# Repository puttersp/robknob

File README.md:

# robknob
## Robknob is a smartknob for robotics.
### FEATURES
- Smartknob with Haptic feedback
    - 3 Hapfic feedback modes
        - Fine steps with low detents
        - Rough steps with medium detents
        - Fine steps with medium detents and Bounded with high detents
    - Press for mode change
        - 3 steps press with strain gauges
            - Different colors displayed by LED Strips for different steps
        - LiDAR Mode for Robot Navigation
        - PID Tuning Mode
        - IMU Display
    - 240x240 Round LCD Display
- LiDAR with 4000Hz Sampling Rate 5M Range
- 6-DOF IMU for Robot Navigation
- ROS2 Compatible

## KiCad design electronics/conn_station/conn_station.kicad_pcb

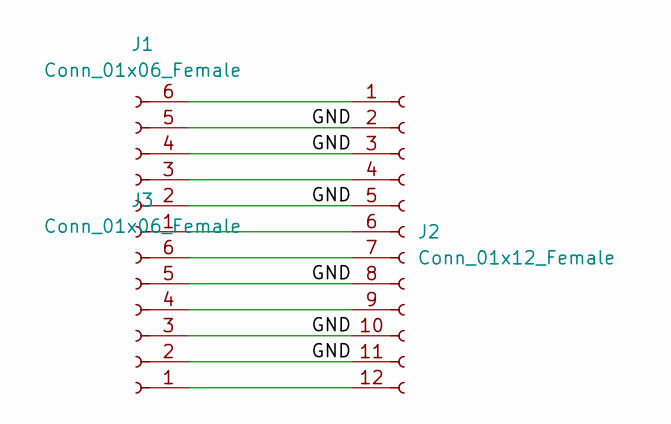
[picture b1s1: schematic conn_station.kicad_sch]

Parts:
J1, J3: Conn_01x06_Female; PinSocket_1x06_P2.54mm_Horizontal
J2: Conn_01x12_Female; Molex_200528-0120_1x12-1MP_P1.00mm_Horizontal

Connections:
/GND: J1.2, J1.4, J1.5, J2.2, J2.3, J2.5, J2.8, J2.10, J2.11, J2.MP, J3.2, J3.3, J3.5
unnamed: J1.1, J2.6
unnamed: J1.3, J2.4
unnamed: J1.6, J2.1
unnamed: J2.7, J3.6
unnamed: J2.9, J3.4
unnamed: J2.12, J3.1

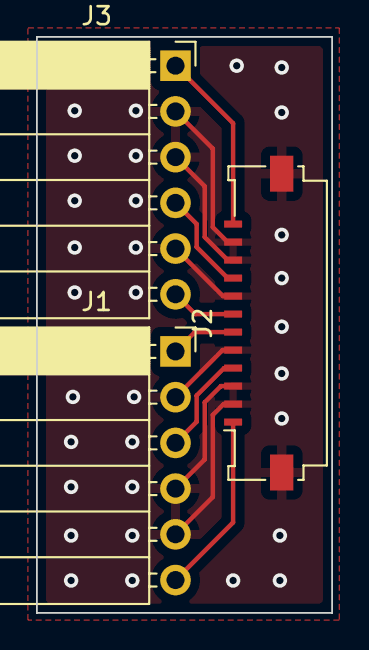
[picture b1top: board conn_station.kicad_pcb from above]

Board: 2 copper layers, 16.4 x 32.0 mm, 3 parts (0 on the bottom side), 7 nets.

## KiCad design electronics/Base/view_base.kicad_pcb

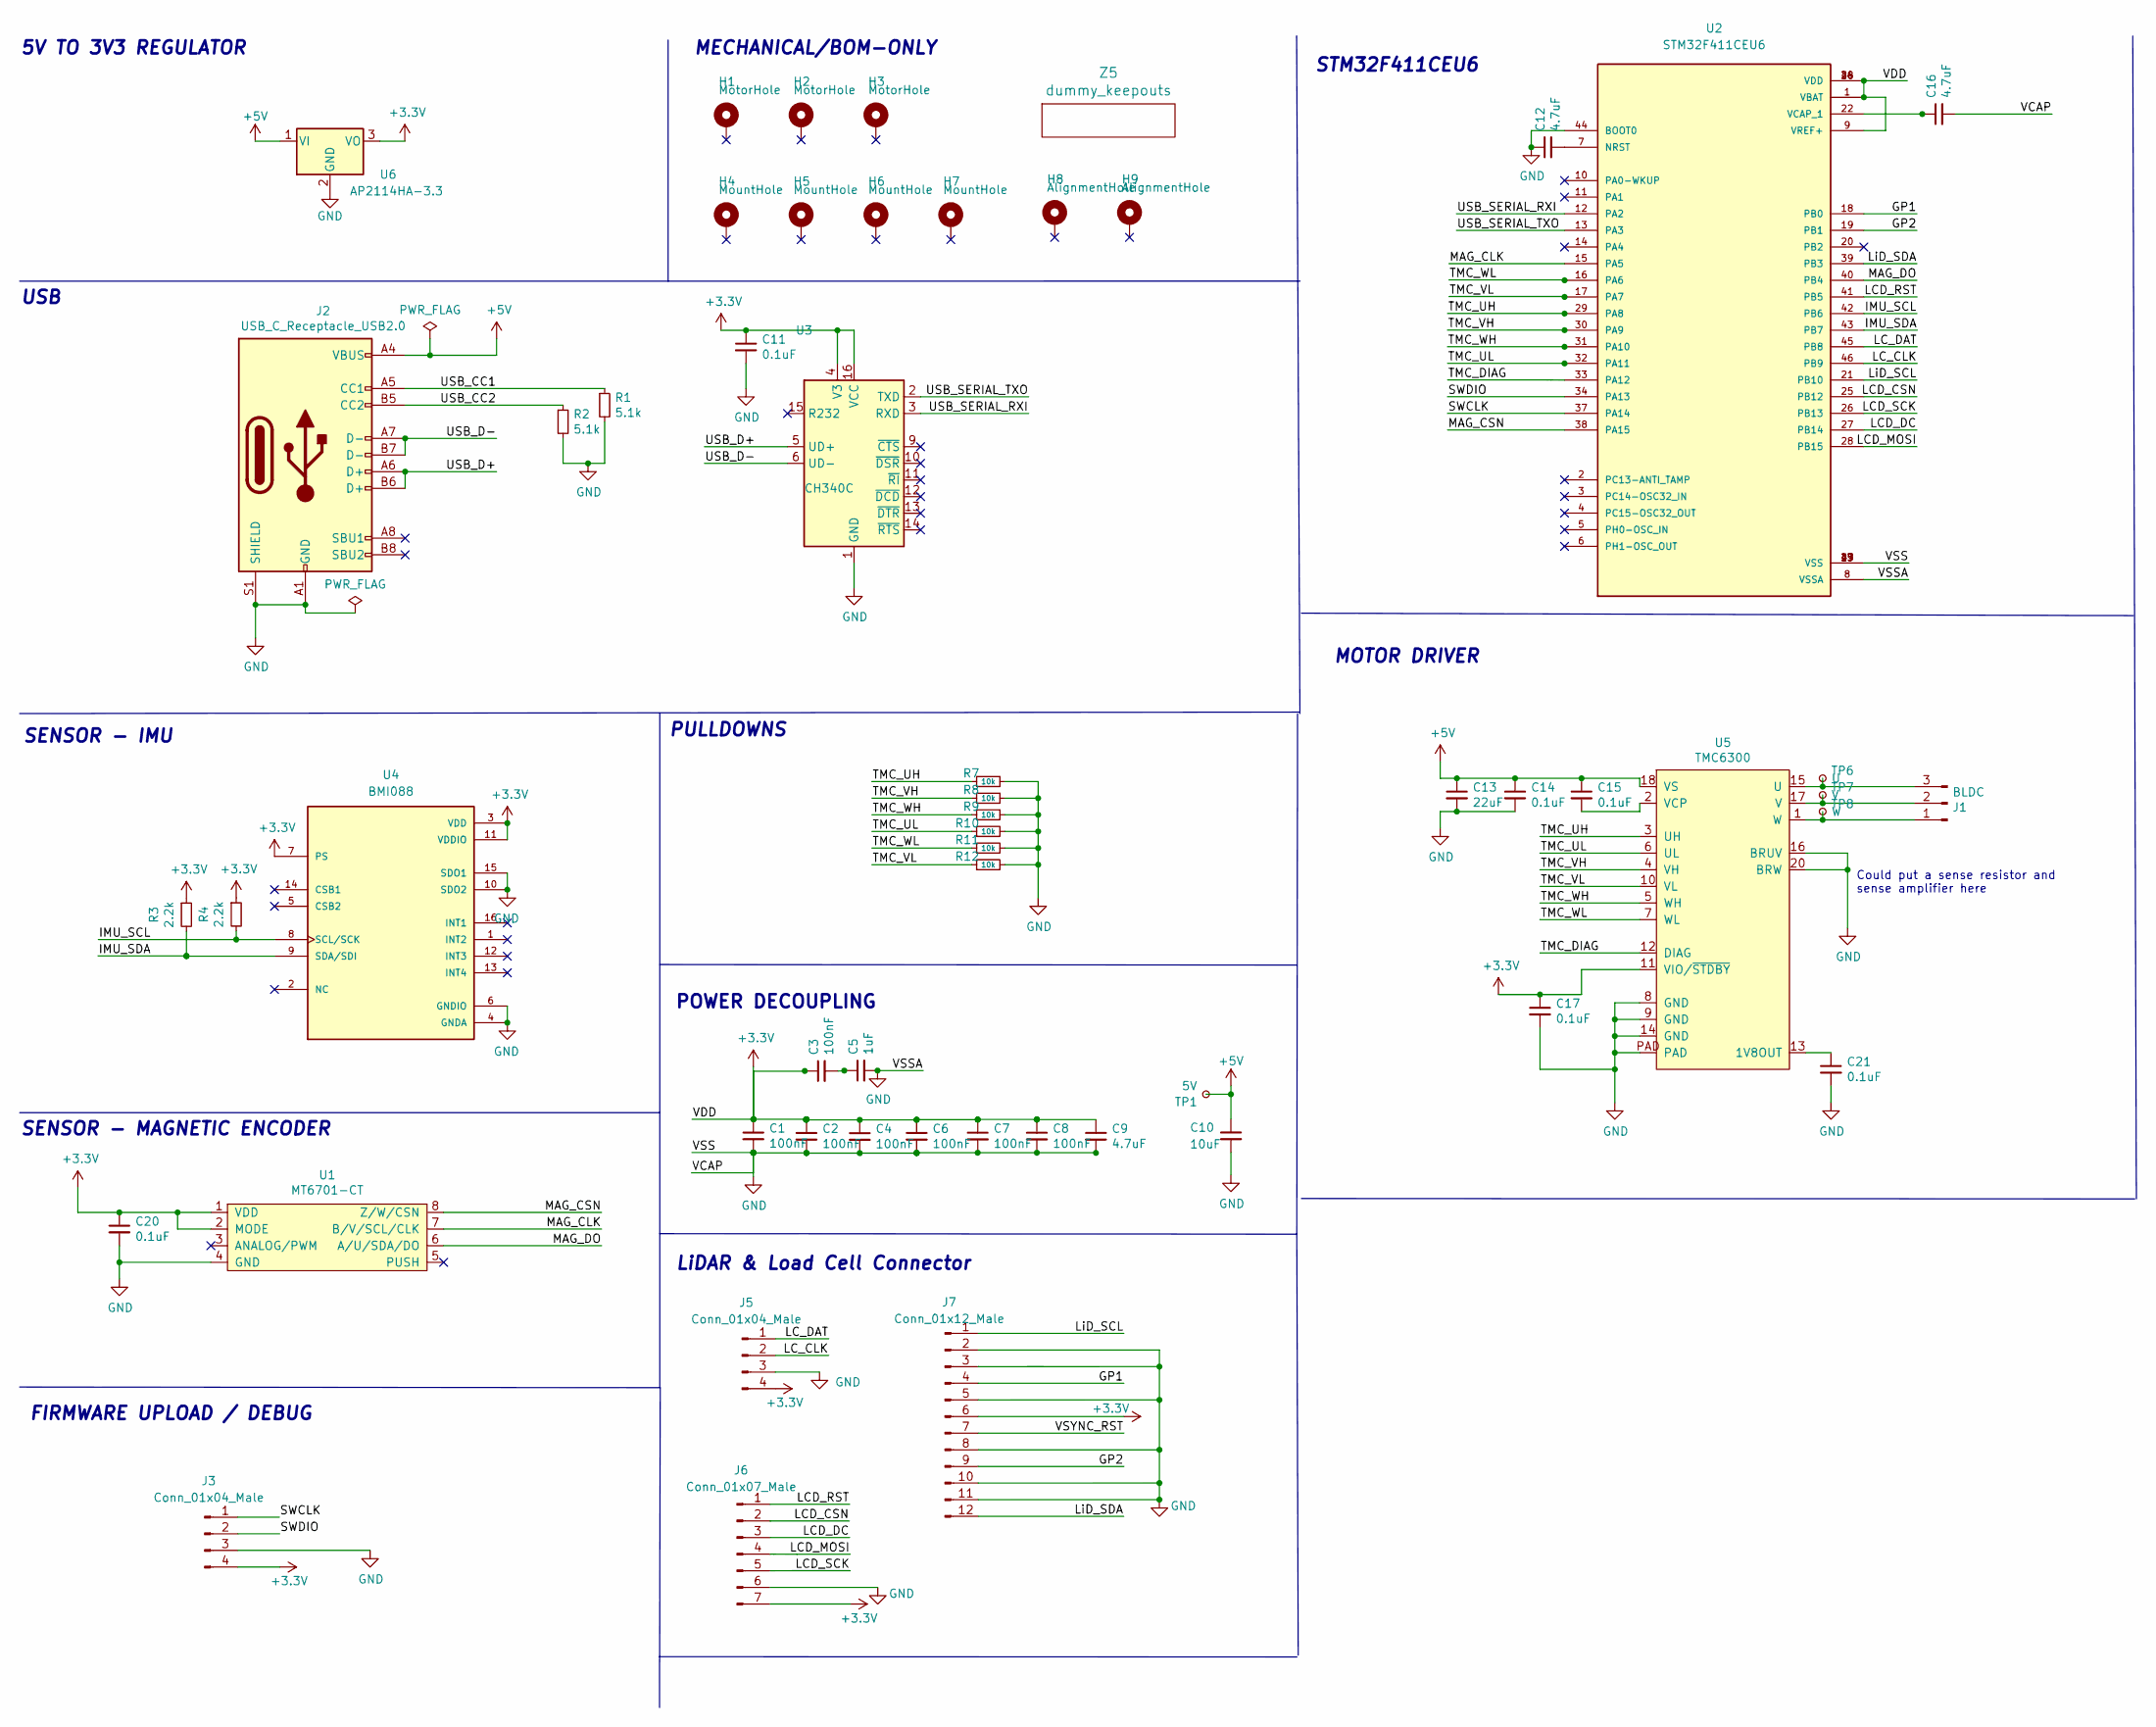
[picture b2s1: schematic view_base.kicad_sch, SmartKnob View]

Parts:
C1, C2, C3, C4, C6, C7, C8: 100nF; C_0603_1608Metric; LCSC C1591
C5: 1uF; C_0603_1608Metric; LCSC C1591
C9, C12, C16: 4.7uF; C_0603_1608Metric; LCSC C1591
C10: 10uF; C_0805_2012Metric; LCSC C2922480
C11, C14, C15, C17, C20, C21: 0.1uF; C_0603_1608Metric; LCSC C1591
C13: 22uF; C_0805_2012Metric; LCSC C98190
H1, H2, H3: MotorHole; MountingHole_M1.6; LCSC C2931389
H4, H5, H6, H7: MountHole; MountingHole_2.2mm_M2_ISO7380_Pad_NonVirtual; LCSC C2911210 or C2911532 (screw), C2961595 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
H8, H9: AlignmentHole; MountingHole_2.2mm_M2_ISO7380_Pad_NonVirtual
J1: BLDC; 532610371; LCSC C293630
J2: USB_C_Receptacle_USB2.0; USB4510_NoPaste; LCSC C428463
J3, J5: Conn_01x04_Male; PinHeader_1x04_P2.54mm_Vertical
J6: Conn_01x07_Male; PinHeader_1x07_P2.54mm_Vertical
J7: Conn_01x12_Male; Molex_200528-0120_1x12-1MP_P1.00mm_Horizontal
R1, R2: 5.1k; R_0603_1608Metric; LCSC C105580
R3, R4: 2.2k; R_0603_1608Metric; LCSC C4190
R7, R8, R9, R10, R11, R12: 10k; R_0603_1608Metric; LCSC C98220
TP1: 5V; TestPoint_Pad_D2.0mm_ValueSilk
TP6: U; TestPoint_Pad_D2.0mm_ValueSilk
TP7: V; TestPoint_Pad_D2.0mm_ValueSilk
TP8: W; TestPoint_Pad_D2.0mm_ValueSilk
U1: MT6701-CT; SOIC-8_3.9x4.9mm_P1.27mm; LCSC C2856764, or C3003196
U2: STM32F411CEU6; QFN50P700X700X60-49N; PARTREV 7
U3: CH340C; SOIC-16_3.9x9.9mm_P1.27mm; LCSC C84681
U4: BMI088; PQFN50P450X300X100-16N
U5: TMC6300; QFN-20-1EP_3x3mm_P0.4mm_EP1.65x1.65mm_ThermalVias_LargerVia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; Digikey TMC6300-LA-T
U6: AP2114HA-3.3; SOT-223-3_TabPin2_InGndOut; LCSC C460314
Z5: dummy_keepouts; ViewKeepouts3d

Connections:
+3V3: C1.1, C2.1, C3.1, C4.1, C6.1, C7.1, C8.1, C9.1, C11.1, C17.1, C20.1, J3.4, J5.4, J6.7, J7.6, R3.1, R4.1, U1.1 (VDD), U1.2 (MODE), U2.1 (VBAT), U2.9 (VREF+), U2.24 (VDD), U2.36 (VDD), U2.48 (VDD), U3.4 (V3), U3.16 (VCC), U4.3 (VDD), U4.7 (PS), U4.11 (VDDIO), U5.11 (VIO/~STDBY), U6.3 (VO)
+5V: C10.1, C13.1, C14.1, C15.1, J2.A4 (VBUS), J2.A9 (VBUS), J2.B4 (VBUS), J2.B9 (VBUS), TP1.1, U5.18 (VS), U6.1 (VI)
/GP1: J7.4, U2.18 (PB0)
/GP2: J7.9, U2.19 (PB1)
/IMU_SCL: R4.2, U2.42 (PB6), U4.8 (SCL/SCK)
/IMU_SDA: R3.2, U2.43 (PB7), U4.9 (SDA/SDI)
/LCD_CSN: J6.2, U2.25 (PB12)
/LCD_DC: J6.3, U2.27 (PB14)
/LCD_MOSI: J6.4, U2.28 (PB15)
/LCD_RST: J6.1, U2.41 (PB5)
/LCD_SCK: J6.5, U2.26 (PB13)
/LC_CLK: J5.2, U2.46 (PB9)
/LC_DAT: J5.1, U2.45 (PB8)
/LiD_SCL: J7.1, U2.21 (PB10)
/LiD_SDA: J7.12, U2.39 (PB3)
/MAG_CLK: U1.7 (B/V/SCL/CLK), U2.15 (PA5)
/MAG_CSN: U1.8 (Z/W/CSN), U2.38 (PA15)
/MAG_DO: U1.6 (A/U/SDA/DO), U2.40 (PB4)
/SWCLK: J3.1, U2.37 (PA14)
/SWDIO: J3.2, U2.34 (PA13)
/TMC_DIAG: U2.33 (PA12), U5.12 (DIAG)
/TMC_UH: R7.1, U2.29 (PA8), U5.3 (UH)
/TMC_UL: R10.1, U2.32 (PA11), U5.6 (UL)
/TMC_VH: R8.1, U2.30 (PA9), U5.4 (VH)
/TMC_VL: R12.1, U2.17 (PA7), U5.10 (VL)
/TMC_WH: R9.1, U2.31 (PA10), U5.5 (WH)
/TMC_WL: R11.1, U2.16 (PA6), U5.7 (WL)
/USB_CC1: J2.A5 (CC1), R1.1
/USB_CC2: J2.B5 (CC2), R2.1
/USB_D+: J2.A6 (D+), J2.B6 (D+), U3.5 (UD+)
/USB_D-: J2.A7 (D-), J2.B7 (D-), U3.6 (UD-)
/USB_SERIAL_RXI: U2.12 (PA2), U3.3 (RXD)
/USB_SERIAL_TXO: U2.13 (PA3), U3.2 (TXD)
/VSYNC_RST: J7.7
GND: C1.2, C2.2, C4.2, C5.2, C6.2, C7.2, C8.2, C9.2, C10.2, C11.2, C12.1, C13.2, C14.2, C16.2, C17.2, C20.2, C21.2, J2.A1 (GND), J2.A12 (GND), J2.B1 (GND), J2.B12 (GND), J2.S1 (SHIELD), J3.3, J5.3, J6.6, J7.2, J7.3, J7.5, J7.8, J7.10, J7.11, J7.MP, R1.2, R2.2, R7.2, R8.2, R9.2, R10.2, R11.2, R12.2, U1.4 (GND), U2.8 (VSSA), U2.23 (VSS), U2.35 (VSS), U2.44 (BOOT0), U2.47 (VSS), U2.49 (VSS), U3.1 (GND), U4.4 (GNDA), U4.6 (GNDIO), U4.10 (SDO2), U4.15 (SDO1), U5.8 (GND), U5.9 (GND), U5.14 (GND), U5.16 (BRUV), U5.20 (BRW), U5.PAD, U6.2 (GND)
unnamed: C3.2, C5.1
unnamed: C12.2, U2.7 (NRST)
unnamed: C15.2, U5.2 (VCP)
unnamed: C16.1, U2.22 (VCAP_1)
unnamed: C21.1, U5.13 (1V8OUT)
unnamed: J1.1, TP8.1, U5.1 (W)
unnamed: J1.2, TP7.1, U5.17 (V)
unnamed: J1.3, TP6.1, U5.15 (U)

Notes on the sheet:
5V TO 3V3 REGULATOR
Could put a sense resistor and sense amplifier here
STM32F411CEU6
SENSOR - MAGNETIC ENCODER
MOTOR DRIVER
MECHANICAL/BOM-ONLY
POWER DECOUPLING
LiDAR & Load Cell Connector
USB
SENSOR - IMU
PULLDOWNS
FIRMWARE UPLOAD / DEBUG

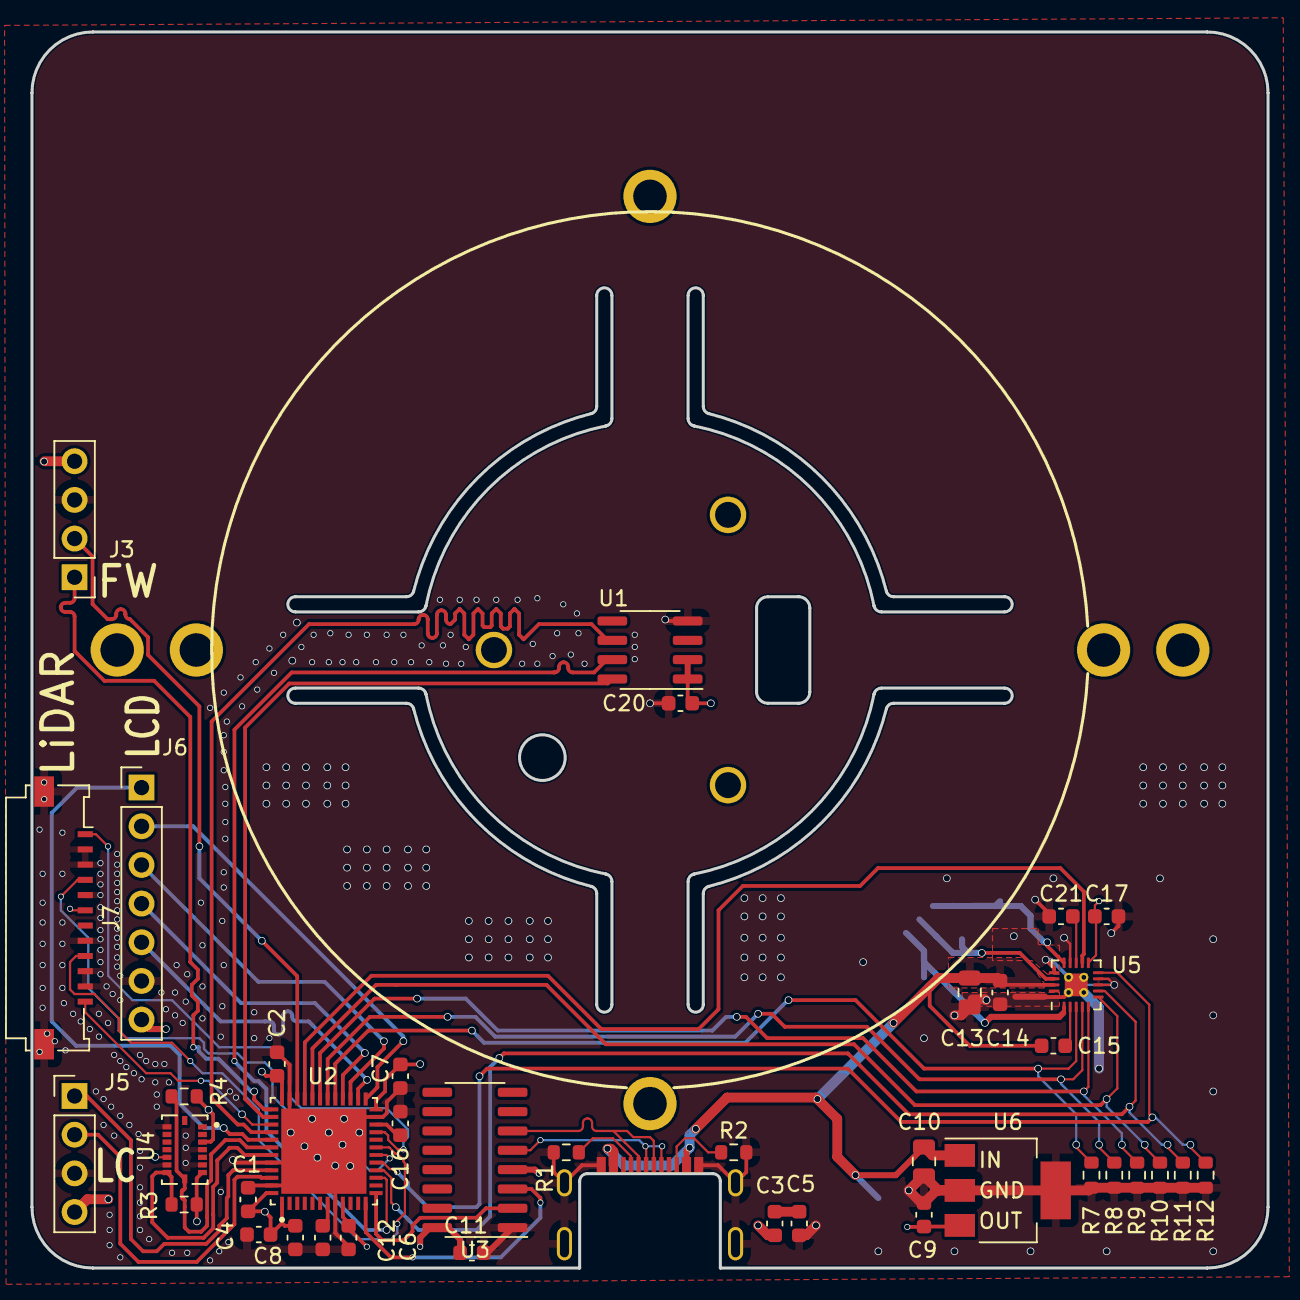
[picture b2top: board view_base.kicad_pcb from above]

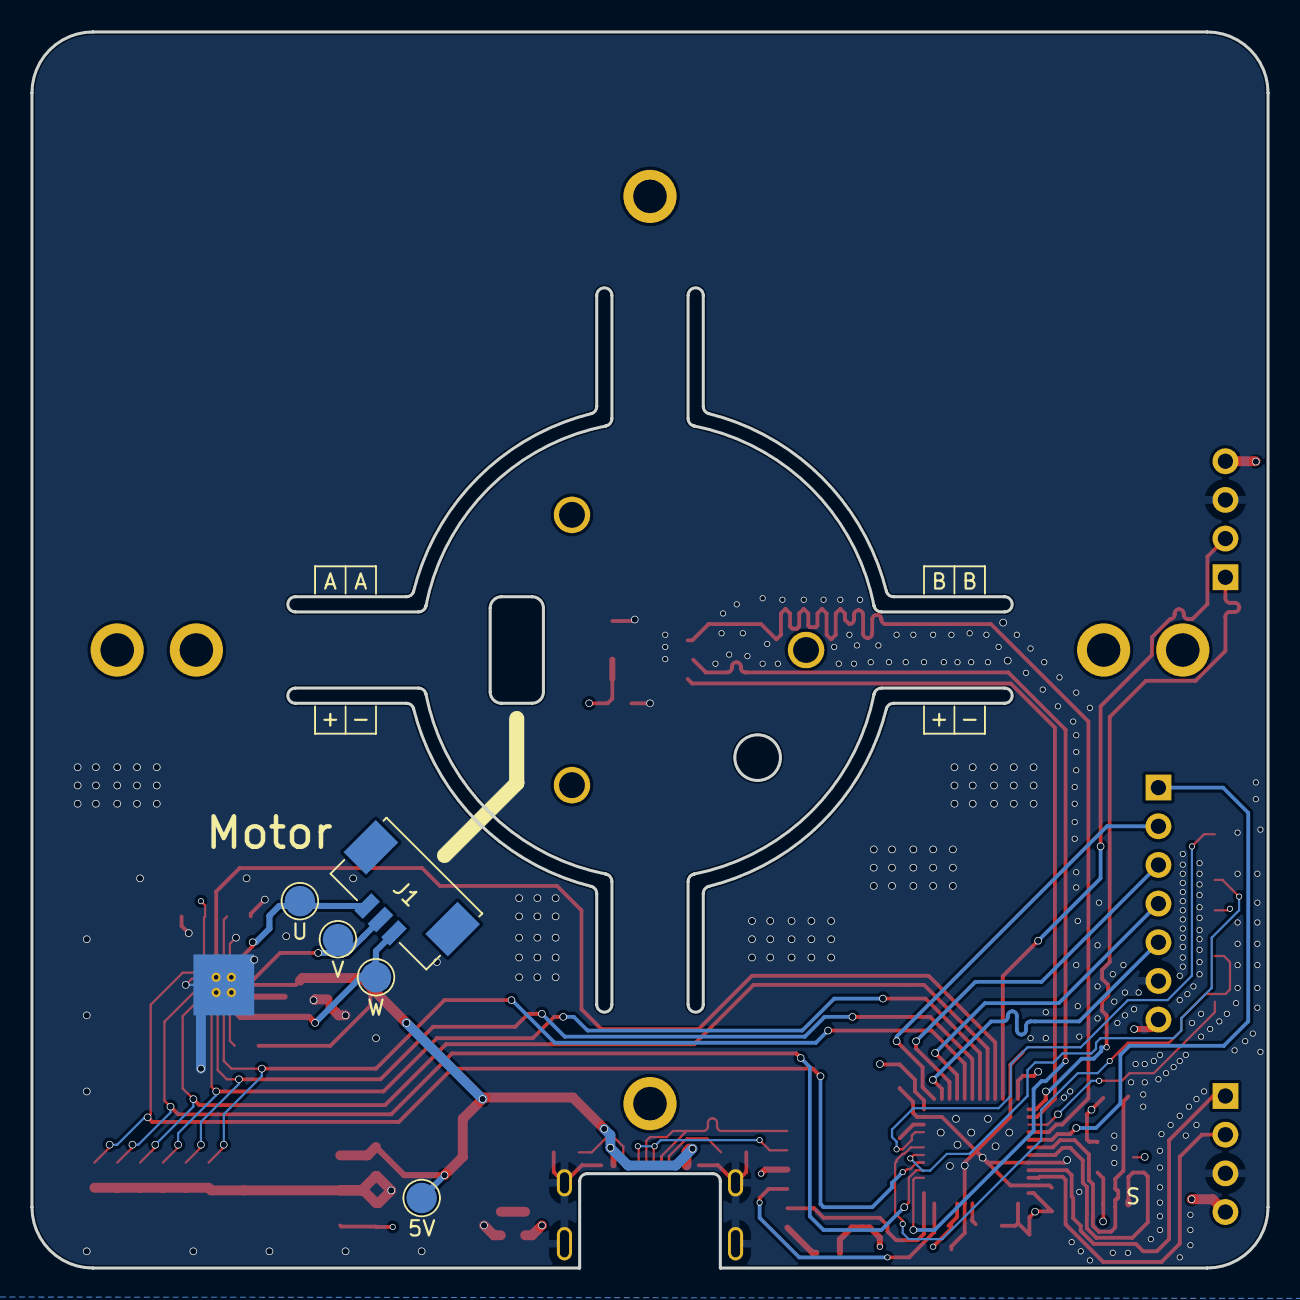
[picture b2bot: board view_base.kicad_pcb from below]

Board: 4 copper layers, 81.2 x 81.2 mm, 55 parts (5 on the bottom side), 42 nets.

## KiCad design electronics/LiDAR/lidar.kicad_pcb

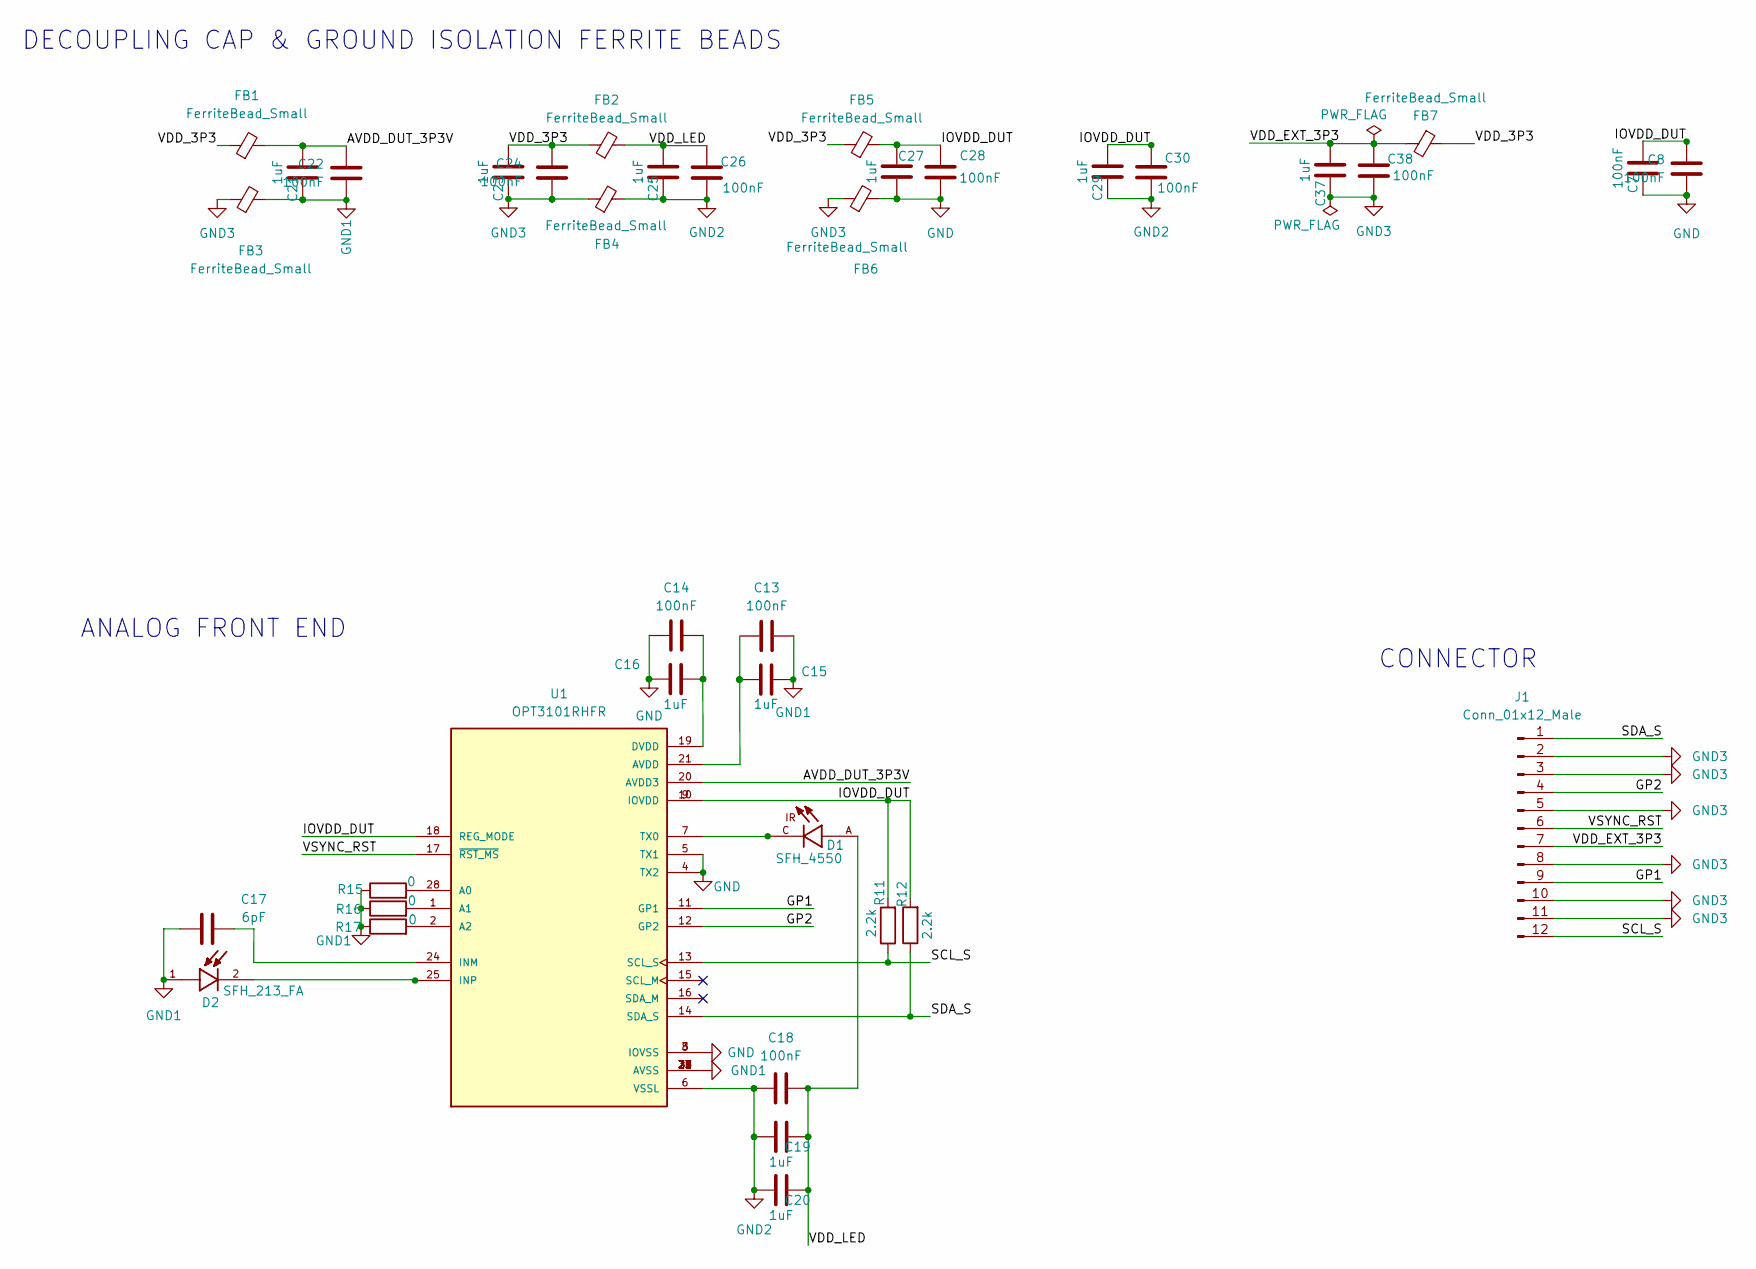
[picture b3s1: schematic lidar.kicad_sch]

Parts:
C7, C8, C13, C14, C18, C22, C24, C26, C28, C30, C38: 100nF; C_0402_1005Metric
C15, C16, C19, C20, C21, C23, C25, C27, C29, C37: 1uF; C_0402_1005Metric
C17: 6pF; C_0201_0603Metric
D1: SFH_4550; DIO_SFH_4550; PARTREV 1.6
D2: SFH_213_FA; XDCR_SFH_213_FA; PARTREV 1.3
FB1, FB2, FB3, FB4, FB5, FB6, FB7: FerriteBead_Small; BEADC1005X50N
J1: Conn_01x12_Male; Molex_200528-0120_1x12-1MP_P1.00mm_Horizontal
R11, R12: 2.2k; R_0402_1005Metric
R15, R16, R17: 0; R_0402_1005Metric
U1: OPT3101RHFR; IC_OPT3101RHFR; PARTREV A

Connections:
/AVDD_DUT_3P3V: C21.1, C22.2, FB1.2, U1.20 (AVDD3)
/GP1: J1.9, U1.11 (GP1)
/GP2: J1.4, U1.12 (GP2)
/IOVDD_DUT: C7.1, C8.2, C27.1, C28.2, C29.1, C30.2, FB5.2, R11.2, R12.2, U1.9 (IOVDD), U1.10 (IOVDD), U1.18 (REG_MODE)
/SCL_S: J1.12, R11.1, U1.13 (SCL_S)
/SDA_S: J1.1, R12.1, U1.14 (SDA_S)
/VDD_3P3: C23.1, C24.2, FB1.1, FB2.1, FB5.1, FB7.1
/VDD_EXT_3P3: C37.1, C38.2, FB7.2, J1.7
/VDD_LED: C18.1, C19.2, C20.2, C25.1, C26.2, D1.A, FB2.2
/VSYNC_RST: J1.6, U1.17 (~RST_MS)
GND: C7.2, C8.1, C14.2, C16.1, C27.2, C28.1, FB6.2, U1.3 (IOVSS), U1.4 (TX2), U1.5 (TX1), U1.8 (IOVSS)
GND1: C13.1, C15.2, C17.1, C21.2, C22.1, D2.1, FB3.2, R15.1, R16.1, R17.1, U1.23 (AVSS), U1.26 (AVSS), U1.27 (AVSS), U1.29 (AVSS), U1.30 (AVSS), U1.31 (AVSS), U1.32 (AVSS), U1.33 (AVSS), U1.34 (AVSS)
GND2: C18.2, C19.1, C20.1, C25.2, C26.1, C29.2, C30.1, FB4.2, U1.6 (VSSL)
GND3: C23.2, C24.1, C37.2, C38.1, FB3.1, FB4.1, FB6.1, J1.2, J1.3, J1.5, J1.8, J1.10, J1.11
unnamed: C13.2, C15.1, U1.21 (AVDD)
unnamed: C14.1, C16.2, U1.19 (DVDD)
unnamed: C17.2, U1.24 (INM)
unnamed: D1.C, U1.7 (TX0)
unnamed: D2.2, U1.25 (INP)
unnamed: R15.2, U1.28 (A0)
unnamed: R16.2, U1.1 (A1)
unnamed: R17.2, U1.2 (A2)

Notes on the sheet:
ANALOG FRONT END
DECOUPLING CAP & GROUND ISOLATION FERRITE BEADS
CONNECTOR

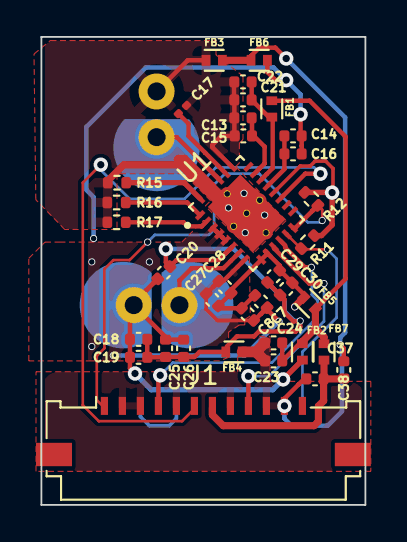
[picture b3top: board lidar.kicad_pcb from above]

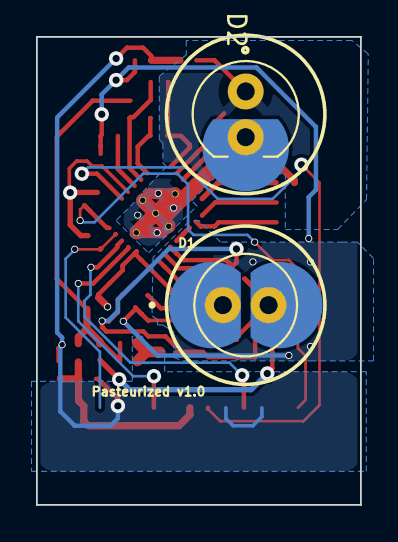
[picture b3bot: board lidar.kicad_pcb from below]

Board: 4 copper layers, 18.0 x 26.0 mm, 38 parts (2 on the bottom side), 22 nets.

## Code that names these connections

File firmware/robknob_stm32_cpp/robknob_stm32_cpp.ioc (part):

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Mcu.Name=STM32F411C(C-E)Ux
Mcu.Package=UFQFPN48
Mcu.UserName=STM32F411CEUx
PA0-WKUP.Mode=SYS_WakeUp0
PA0-WKUP.Signal=SYS_WKUP
PA10.Signal=S_TIM1_CH3
PA11.Signal=S_TIM1_CH4
PA12.Signal=GPIO_Input
PA13.Mode=Serial_Wire
PA13.Signal=SYS_JTMS-SWDIO
PA14.Mode=Serial_Wire
PA14.Signal=SYS_JTCK-SWCLK
PA15.GPIOParameters=GPIO_PuPd
PA15.GPIO_PuPd=GPIO_PULLUP
PA15.Signal=GPIO_Output
PA2.Mode=Asynchronous
PA2.Signal=USART2_TX
PA3.Mode=Asynchronous
PA3.Signal=USART2_RX
PA5.Mode=Full_Duplex_Master
PA5.Signal=SPI1_SCK
PA6.Signal=S_TIM3_CH1
PA7.Signal=S_TIM3_CH2
PA8.Signal=S_TIM1_CH1
PA9.Signal=S_TIM1_CH2
PB0.Signal=GPIO_Input
PB1.Signal=GPIO_Input
PB10.Mode=I2C
PB10.Signal=I2C2_SCL
PB3.Mode=I2C
PB3.Signal=I2C2_SDA
PB4.Mode=Full_Duplex_Master
PB4.Signal=SPI1_MISO
PB5.Mode=Full_Duplex_Master
PB5.Signal=SPI1_MOSI
PB6.Mode=I2C
PB6.Signal=I2C1_SCL
PB7.Mode=I2C
PB7.Signal=I2C1_SDA
RCC.HSE_VALUE=25000000
RCC.SYSCLKFreq_VALUE=16000000
board=custom

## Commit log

2023-11-23 Cad & Elec
2023-11-23 KICAD's footprint/symbol/cad
2024-01-09 add stuff
2024-01-09 creating stm32 firmware & setting up IOC
2024-01-10 SimpleFOC porting done
2024-01-10 Converted fully to CPP

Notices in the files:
parts and their libraries:
Copyright 2021 Accelerated Designs. All rights reserved.
